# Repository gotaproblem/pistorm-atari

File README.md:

# PiStorm 4 Atari

# Join us on Discord

* There's a Discord server dedicated to PiStorm Atari discussion and development, which you can join through this handy invite link: https://discord.gg/XFEBA8QDzQ

* **IMPORTANT NOTE: Selling blank or complete PCBs or derivatives on eBay or elsewhere for excessive profit is frowned upon and may lead to forthcoming related projects being closed source.**
* Even with the current global chip shortage (October 2021), components are not **so** expensive that you should pay up to a hundred dollars or Euros for a board.
* The PiStorm is not a project for making money, it is meant to be an affordable way to replace and extend the functionality of EOL Motorola 68000 processors and have fun in the process.
* This is not meant to discourage you from making PiStorm boards for others to enjoy, but for instance selling the product as a commercial item and then pawning off support to the community if something doesn't work is absolutely not good™.

# Project information

* This fork is solely for the Atari platform. All Amiga code has been removed.
* Development is ongoing on an Atari STe, utilising an exxos PLLC adapter board to allow the fitting of the PiStorm interface. The ongoing work is a "proof-of-concept". If proven to offer acceptable performance, then bespoke hardware will be needed to allow installation within the confines of the Atari ST platforms. **If you are lucky enough to own a Phoenix H5 board (exxos shop), then the PiStorm with Pi4 fits nicely :)**
* The Atari platform differs greatly to the Amiga platform. The Atari ST uses the FC signals, interrups and bus arbitration.
* ~~Initial development was on a PI3B, but performance was poor. A PI3A+ was tried and again the performance was poor. Finally, a PI4B was tried. Although initial performance was still poor in comparison to the Amiga, there was headroom for improvemnt. Over many months, performance has slowly increased, and at time of writing, performance is finally acceptable.~~

**NOTE**

The current builds require a Pi4. This hopefully will change once a stable solution is found.
The current firmware may not work with PiSTorm boards using 74LVC16374 latches. It's a case of trying and seeing. All efforts are being made to correct this.

~~PiStorm must have 374 latches. Any other are known not to be compatible for the moment.~~
~~Sep 2023 - Firmware development has resolved the different latch/flip-flop type dependancy. Meaning, both 373 and 374 parts now work.~~
~~Sep 2023 - Pi3A+ now offers acceptible performance~~
~~Oct 2023 - Pi3B is working but needs to be overclocked~~
~~Oct 2023 - Pi Zero 2W is working but needs to be overslocked~~

Jun 2025 - Only use the latest branch. Anything before the jan2025 branch is obsolete

# Extended functionality

A virtual IDE interface is included which allows for two disk drive images to be attached, each up to 8GB in size. 
**UPDATE Oct 2023**
An additional three virtual IDE interfaces are now included, allowing for a total of eight disk drive images - a potential 64GB of disk space.

* Atari ST ROM images can be loaded at initialisation. For example, the emulation can boot using TOS 1.04 (ST only), TOS 1.06, TOS 1.62, TOS 2.06 or even EMUTos
* Alt-RAM/TT-RAM option can be added (68020, 68030, 68040 only), to increase performance
* 68020 CPU can be used with an FPU
* ET4000 SVGA graphics is now available with 1MB VRAM
* Screen grabs can be taken when using ET4000
* Additional interfaces will be added with time

# Now to get up-and-running
The following steps require basic knowledge of the linux operating system. Take your time!

* Download Raspberry Pi OS from https://www.raspberrypi.org/software/operating-systems/, you need the 32 bit Lite version.
**NOTE**
* Atari PiStorm installation has been tested with Bullseye and Bookworm

* Write the Image to an SD card. For development, a 32 GB SD card is recommended.
* Connect an HDMI Display and a USB keyboard to the Raspberry Pi.
* Insert the SD card into the Raspberry Pi4, and connect it to power. You should see a Rainbow colored screen on the HDMI Monitor followed by the booting sequence.
* When the boot process is finished (on the first run it reboots automatically after resizing the filesystems to your SD) you should be greeted with the login prompt.
* Log in as the default user, typically user: `pi` and password: `raspberry`. (The keyboard is set to US Layout on first boot!)
* Run `sudo raspi-config`
* Set up your preferences like keyboard layout, language, etc. It is recommended to set the screen resolution to 1280x720.
* Set up your Wi-Fi credentials
* Enable SSH at boot time
* Exit raspi-config

You can now reach the Pi over SSH, check your router web/settings page to find the IP of the PiStorm, or run `ifconfig` locally on the Pi from the console.

Now the final steps to get things up and running, all of this is done from a command prompt (terminal) either locally on the Pi or over ssh:
* `sudo apt-get update`
* `sudo apt full-upgrade` (If you get mysterious 'not found' messages from running the line in the next step.)
* ~~`sudo apt-get install git libasound2-dev`~~
* `sudo apt-get install git ffmpeg`
* `git clone https://github.com/gotaproblem/pistorm-atari`
* `cd pistorm-atari`
* `make clean`
**NOTE**
If using a Pi3, make must be given an option
* `make PIMODEL=PI3`
If using a Pi4, no option is needed
* `make`

~~**STRAM CACHE**~~
~~The experimental full memory cache-enabled version may be built with~~
~~* `make CACHE=ON`~~
~~or~~
~~* `make POMODEL=PI3 CACHE=ON`~~

~~This feature greatly improves STRAM read operations (and hence is mostly applicable to games), but is not yet compatible with operation of the Blitter, so please disable this at the Desktop.~~

Copy the linux boot configuration file:
* `sudo cp configs/config.txt /boot/`

Append the following to your /boot/cmdline.txt file
* `quiet vt.global_cursor_default=0 fsck.mode=force fsck.repair=yes`
**NOTE**
Do not add new-lines to this file. The entries must be one continuous line

Congratulate yourself - You've gotten this far! Shutdown the linux operating system
* `sudo halt`

# Install the hardware
**Power Caution**

How do you intend to power this thing? There are two possibilities
* 1 - power via the Atari
This is okay for the final-cut, but for development, option 2 is suggested
* 2 - power via USB
If you are developing, which requires numerous power cycles, then this is the option for you. You will need to make sure USB power (5v) does not reach the PiStorm. The Pi GPIO header supplies 5v power on pins 2 and 4. These two pins need to be cut.
As the Pi physically can not connect directly to the PiStorm, a header extension is needed - this is where you cut the pins - **do not cut the pins on the Raspberry Pi header.**
**NOTE**
DO NOT APPLY POWER FROM MULTIPLE SOURCES

If using a Pi4, a Header extension is needed, such as

https://www.amazon.co.uk/gp/product/B08C581XHV/ref=ppx_yo_dt_b_asin_title_o03_s00?ie=UTF8&th=1

https://www.amazon.co.uk/gp/product/B07NQ5Z7Y9/ref=ppx_yo_dt_b_asin_title_o04_s00?ie=UTF8&psc=1

* Attach the Pi to the PiStorm and install the PiStorm adapter in place of the orignal CPU in the Atari.
  Make sure the PiStorm sits flush and correct in the socket.
  Double check that all is properly in place and no pins are bent.

# FPGA bitstream update :
Before we can use the PiStorm, it needs to have firmware installed. 

~~Install OpenOCD:~~
~~**NOTE - v0.11 needed**~~
~~Check your openocd version~~
~~* `openocd -v`~~
~~If you have version 0.12 or later, follow these instructions:~~
~~* `sudo apt-get remove openocd`~~
~~* `sudo apt-get install openocd=0.11.0~rc2-1`~~

~~Run the FPGA update with `./flash.sh`, this will automatically detect your CPLD variant and flash appropriately.~~

~~If successful "Flashing successful!" will appear, if not it will fail with "Flashing failed" and `nprog_log.txt` will be created with more details.~~

Dec 2023 - openocd is no longer used

* Flash the PiStorm firmware using the included tool - replace xxx with your CPLD type eg. EPM240 or EPM570
`rtl/pistormflash -s rtl/EPMxxx_bitstream.svf`
Expect a "Warning" to be shown. This can be ignored.

# Running

**Testing**

As a confidence test, it is suggested you run ataritest to confirm basic functionality.
* `sudo ./ataritest --memory tests=rw`
If you see any errors, then discuss in the discord development channel. 

ataritest can do a lot more, like reading and writing (peek and poke), to Atari memory space, filling Atari memory with patterns.

**Setup file structure**

From the pistorm-atari directory, perform the following commands
* `mkdir ../roms`
* `mkdir ../dkimages`
* `mkdir ../configs`
* `mkdir ../screendumps`
* `cp configs/atari.cfg ../configs`
* `cp roms/roms.zip ../roms/`
* `cd ../roms`
* `unzip roms.zip`
* `cd ../pistorm-atari`

**Starting the Emulator**

Start the emulator with the default Atari configuration by typing `sudo ./emulator --config ../configs/atari.cfg`

A couple of disk images have been created to help you get started. These are optional. You could of course run programmes off your 
floppy disk drive and/or an attached ACSI bus device.

**The disk images are too large for GitHub. Please find the disk images at https://bbansolutions.co.uk**
Download the disks.zip file, copy to ../dkimages/ directory. Uncompress the file to give two disk images.
* `cd ../dkimages`
* `wget http://bbansolutions.co.uk/wp-content/uploads/2023/10/disks.zip`
* `unzip disks.zip`
* `cd ../pistorm-atari`

Run the emulator using `sudo ./emulator --config ../configs/atari.cfg`.

To exit the emulator you can press `Ctrl+C`.

# RTG Graphics ~~- Raylib~~
Sep 2023 - no-longer using raylib

Enhanced video modes are available for GEM and Mint.
* Changes to the emulator configuration file are needed
* edit your .cfg file and uncomment (remove the preceding hash), the following line
* #setvar rtg

**A mint specific configuration file is now included in the repository**
* Make a copy of configs/mint.cfg
* `cp configs/mint.cfg ../configs/`

~~Finally, perform a rebuild~~
~~To build now, using RTG, you must alter the git branch before compiling~~
~~* `git checkout et4000-dev`~~
~~* `make clean`~~
~~* `make`~~

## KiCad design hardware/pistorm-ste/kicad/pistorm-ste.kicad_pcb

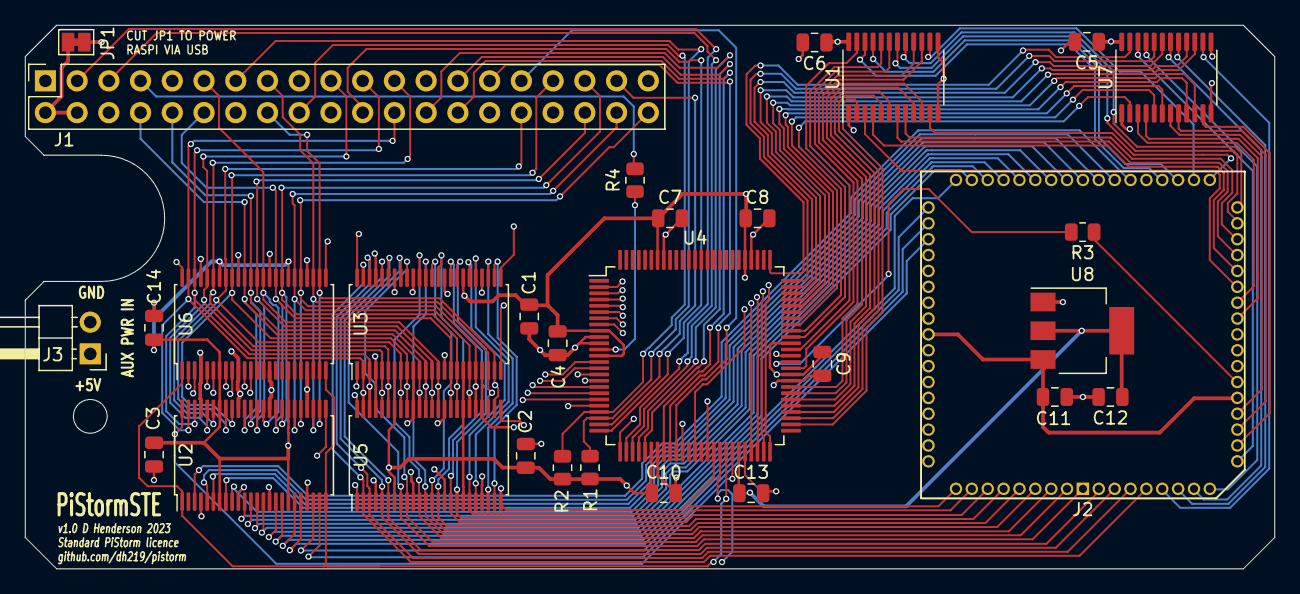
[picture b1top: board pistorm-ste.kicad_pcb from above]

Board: 4 copper layers, 100.0 x 43.5 mm, 30 parts (0 on the bottom side), 125 nets.

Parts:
C1, C2, C3, C4, C5, C6, C7, C8, C9, C10, C13, C14: 100n; C_0805_2012Metric
C11, C12: 22u; C_0805_2012Metric
J1: Raspberry_Pi_2_3; PinSocket_2x20_P2.54mm_Vertical
J2: PLCC68_plug; PLCC68_male_pins
J3: Conn_01x02_Male; PinHeader_1x02_P2.54mm_Horizontal
JP1: SolderJumper_2_Bridged; SolderJumper-2_P1.3mm_Bridged_Pad1.0x1.5mm
R1, R2: 4k7; R_0805_2012Metric
R3, R4: 0-100R; R_0805_2012Metric
U1, U7: SN54CBTD3384; TSSOP-24_4.4x7.8mm_P0.65mm
U2, U3, U5, U6: SN74LVC16373; TSSOP-48_6.1x12.5mm_P0.5mm
U4: EPM240T100; LQFP-100_14x14mm_P0.5mm
U8: LM1117-3.3; SOT-223-3_TabPin2

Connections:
+3V3: C1.1, C2.1, C3.1, C4.1, C7.1, C8.1, C9.1, C10.1, C12.1, C13.1, C14.1, R1.1, R2.1, U2.7 (VCC), U2.18 (VCC), U2.31 (VCC), U2.42 (VCC), U3.7 (VCC), U3.18 (VCC), U3.31 (VCC), U3.42 (VCC), U4.9 (VCCIO1), U4.13 (VCCINT), U4.31 (VCCIO1), U4.45 (VCCIO1), U4.59 (VCCIO2), U4.63 (VCCINT), U4.80 (VCCIO2), U4.94 (VCCIO2), U5.7 (VCC), U5.18 (VCC), U5.31 (VCC), U5.42 (VCC), U6.7 (VCC), U6.18 (VCC), U6.31 (VCC), U6.42 (VCC), U8.2 (VO)
+5V: C5.1, C6.1, C11.1, J2.14, J2.52, J3.1, JP1.1 (A), U1.24 (VCC), U7.24 (VCC), U8.3 (VI)
/+5V_PI: J1.2 (5V), J1.4 (5V), JP1.2 (B)
/A1: J2.32, U2.3 (1Q2)
/A2: J2.33, U2.5 (1Q3)
/A3: J2.34, U2.6 (1Q4)
/A4: J2.35, U2.8 (1Q5)
/A5: J2.36, U2.9 (1Q6)
/A6: J2.37, U2.11 (1Q7)
/A7: J2.38, U2.12 (1Q8)
/A8: J2.39, U2.13 (2Q1)
/A9: J2.40, U2.14 (2Q2)
/A10: J2.41, U2.16 (2Q3)
/A11: J2.42, U2.17 (2Q4)
/A12: J2.43, U2.19 (2Q5)
/A13: J2.44, U2.20 (2Q6)
/A14: J2.45, U2.22 (2Q7)
/A15: J2.46, U2.23 (2Q8)
/A16: J2.47, U6.2 (1Q1)
/A17: J2.48, U6.3 (1Q2)
/A18: J2.49, U6.5 (1Q3)
/A19: J2.50, U6.6 (1Q4)
/A20: J2.51, U6.8 (1Q5)
/A21: J2.53, U6.9 (1Q6)
/A22: J2.54, U6.11 (1Q7)
/A23: J2.55, U6.12 (1Q8)
/ADDR_LTCH_0: U2.48 (1LE), U4.44 (IO1_44/DEV_CLRn)
/ADDR_LTCH_8: U2.25 (2LE), U4.42 (IO1_42)
/ADDR_LTCH_16: U4.47 (IO1_47), U6.48 (1LE)
/ADDR_LTCH_24: U4.48 (IO1_48), U6.25 (2LE)
/ADDR_OE: U2.1 (1OE), U2.24 (2OE), U4.43 (IO1_43/DEV_OE), U6.1 (1OE), U6.24 (2OE)
/AS: J2.6, U7.14 (2A1)
/AS_3: U4.72 (IO2_72), U7.15 (2B1)
/AUX0: J1.27 (ID_SD/GPIO0), U4.30 (IO1_30)
/AUX1: J1.28 (ID_SC/GPIO1), U4.33 (IO1_33)
/BERR: J2.24, U1.8 (1A4)
/BERR_3: U1.9 (1B4), U4.55 (IO2_55)
/BG: J2.11, U7.11 (1A5)
/BGACK: J2.12, U7.8 (1A4)
/BGACK_3: U4.70 (IO2_70), U7.9 (1B4)
/BG_3: U4.71 (IO2_71), U7.10 (1B5)
/BR: J2.13, U7.7 (1A3)
/BR_3: U4.69 (IO2_69), U7.6 (1B3)
/CLK: R3.2, U4.62 (IO2_62/GCLK2)
/CLK_STE: J2.15, R3.1
/D0: J2.5, U3.47 (1D1), U5.2 (1Q1)
/D1: J2.4, U3.46 (1D2), U5.3 (1Q2)
/D2: J2.3, U3.44 (1D3), U5.5 (1Q3)
/D3: J2.2, U3.43 (1D4), U5.6 (1Q4)
/D4: J2.1, U3.41 (1D5), U5.8 (1Q5)
/D5: J2.68, U3.40 (1D6), U5.9 (1Q6)
/D6: J2.67, U3.38 (1D7), U5.11 (1Q7)
/D7: J2.66, U3.37 (1D8), U5.12 (1Q8)
/D8: J2.65, U3.36 (2D1), U5.13 (2Q1)
/D9: J2.64, U3.35 (2D2), U5.14 (2Q2)
/D10: J2.63, U3.33 (2D3), U5.16 (2Q3)
/D11: J2.62, U3.32 (2D4), U5.17 (2Q4)
/D12: J2.61, U3.30 (2D5), U5.19 (2Q5)
/D13: J2.60, U3.29 (2D6), U5.20 (2Q6)
/D14: J2.59, U3.27 (2D7), U5.22 (2Q7)
/D15: J2.58, U3.26 (2D8), U5.23 (2Q8)
/DATA_RD_LTCH_HB: U3.25 (2LE), U4.50 (IO1_50)
/DATA_RD_LTCH_LB: U3.48 (1LE), U4.49 (IO1_49)
/DATA_RD_OE: U3.1 (1OE), U3.24 (2OE), U4.38 (IO1_38)
/DATA_WR_LTCH_HB: U4.36 (IO1_36), U5.25 (2LE)
/DATA_WR_LTCH_LB: U4.40 (IO1_40), U5.48 (1LE)
/DATA_WR_OE: U4.41 (IO1_41), U5.1 (1OE), U5.24 (2OE)
/DTACK: J2.10, U7.22 (2A5)
/DTACK_3: U4.76 (IO2_76), U7.23 (2B5)
/E: J2.22, U1.4 (1A2)
/E_3: U1.5 (1B2), U4.53 (IO2_53)
/FC0: J2.30, U1.22 (2A5)
/FC0_3: U1.23 (2B5), U4.66 (IO2_66)
/FC1: J2.29, U1.21 (2A4)
/FC1_3: U1.20 (2B4), U4.64 (IO2_64/GCLK3)
/FC2: J2.28, U1.14 (2A1)
/FC2_3: U1.15 (2B1), U4.57 (IO2_57)
/HALT: J2.19, U7.4 (1A2)
/HALT_3: U4.68 (IO2_68), U7.5 (1B2)
/IPL0: J2.27, U1.11 (1A5)
/IPL0_3: U1.10 (1B5), U4.56 (IO2_56)
/IPL1: J2.26, U1.17 (2A2)
/IPL1_3: U1.16 (2B2), U4.58 (IO2_58)
/IPL2: J2.25, U1.18 (2A3)
/IPL2_3: U1.19 (2B3), U4.61 (IO2_61)
/LDS: J2.8, U7.18 (2A3)
/LDS_3: U4.74 (IO2_74), U7.19 (2B3)
/PICLK: R4.2, U4.12 (IO1_12/GCLK0)
/PICLK_OUT: J1.7 (GCLK0/GPIO4), R4.1
/RESET: J2.20, U7.3 (1A1)
/RESET_3: U4.67 (IO2_67), U7.2 (1B1)
/RW: J2.9, U7.21 (2A4)
/RW_3: U4.75 (IO2_75), U7.20 (2B4)
/SA0: J1.29 (GCLK1/GPIO5), U4.34 (IO1_34)
/SA1: J1.5 (SCL/GPIO3), U4.28 (IO1_28)
/SA2: J1.3 (SDA/GPIO2), U4.27 (IO1_27)
/SD0: J1.24 (~CE0/GPIO8), U2.47 (1D1), U3.2 (1Q1), U4.2 (IO1_2), U5.47 (1D1), U6.47 (1D1)
/SD1: J1.21 (MISO0/GPIO9), U2.46 (1D2), U3.3 (1Q2), U4.3 (IO1_3), U5.46 (1D2), U6.46 (1D2)
/SD2: J1.19 (MOSI0/GPIO10), U2.44 (1D3), U3.5 (1Q3), U4.4 (IO1_4), U5.44 (1D3), U6.44 (1D3)
/SD3: J1.23 (SCLK0/GPIO11), U2.43 (1D4), U3.6 (1Q4), U4.5 (IO1_5), U5.43 (1D4), U6.43 (1D4)
/SD4: J1.32 (PWM0/GPIO12), U2.41 (1D5), U3.8 (1Q5), U4.6 (IO1_6), U5.41 (1D5), U6.41 (1D5)
/SD5: J1.33 (PWM1/GPIO13), U2.40 (1D6), U3.9 (1Q6), U4.7 (IO1_7), U5.40 (1D6), U6.40 (1D6)
/SD6: J1.8 (GPIO14/TXD), U2.38 (1D7), U3.11 (1Q7), U4.26 (IO1_26), U5.38 (1D7), U6.38 (1D7)
/SD7: J1.10 (GPIO15/RXD), U2.37 (1D8), U3.12 (1Q8), U4.21 (IO1_21), U5.37 (1D8), U6.37 (1D8)
/SD8: J1.36 (GPIO16), U2.36 (2D1), U3.13 (2Q1), U4.17 (IO1_17), U5.36 (2D1), U6.36 (2D1)
/SD9: J1.11 (GPIO17), U2.35 (2D2), U3.14 (2Q2), U4.16 (IO1_16), U5.35 (2D2), U6.35 (2D2)
/SD10: J1.12 (GPIO18/PWM0), U2.33 (2D3), U3.16 (2Q3), U4.20 (IO1_20), U5.33 (2D3), U6.33 (2D3)
/SD11: J1.35 (GPIO19/MISO1), U2.32 (2D4), U3.17 (2Q4), U4.8 (IO1_8), U5.32 (2D4), U6.32 (2D4)
/SD12: J1.38 (GPIO20/MOSI1), U2.30 (2D5), U3.19 (2Q5), U4.15 (IO1_15), U5.30 (2D5), U6.30 (2D5)
/SD13: J1.40 (GPIO21/SCLK1), U2.29 (2D6), U3.20 (2Q6), U4.14 (IO1_14/GCLK1), U5.29 (2D6), U6.29 (2D6)
/SD14: J1.15 (GPIO22), U2.27 (2D7), U3.22 (2Q7), U4.19 (IO1_19), U5.27 (2D7), U6.27 (2D7)
/SD15: J1.16 (GPIO23), U2.26 (2D8), U3.23 (2Q8), U4.18 (IO1_18), U5.26 (2D8), U6.26 (2D8)
/SOE: J1.31 (GCLK2/GPIO6), U4.35 (IO1_35)
/SWE: J1.26 (~CE1/GPIO7), U4.29 (IO1_29)
/TCK: J1.37 (GPIO26), U4.24 (TCK)
/TDI: J1.13 (GPIO27), R1.2, U4.23 (TDI)
/TDO: J1.22 (GPIO25), U4.25 (TDO)
/TMS: J1.18 (GPIO24), R2.2, U4.22 (TMS)
/UDS: J2.7, U7.17 (2A2)
/UDS_3: U4.73 (IO2_73), U7.16 (2B2)
/VMA: J2.21, U1.3 (1A1)
/VMA_3: U1.2 (1B1), U4.52 (IO2_52)
/VPA: J2.23, U1.7 (1A3)
/VPA_3: U1.6 (1B3), U4.54 (IO2_54)
GND: C1.2, C2.2, C3.2, C4.2, C5.2, C6.2, C7.2, C8.2, C9.2, C10.2, C11.2, C12.2, C13.2, C14.2, J1.6 (GND), J1.9 (GND), J1.14 (GND), J1.20 (GND), J1.25 (GND), J1.30 (GND), J1.34 (GND), J1.39 (GND), J2.16, J2.17, J2.56, J2.57, J3.2, U1.1 (1OE), U1.12 (GND), U1.13 (2OE), U2.4 (GND), U2.10 (GND), U2.15 (GND), U2.21 (GND), U2.28 (GND), U2.34 (GND), U2.39 (GND), U2.45 (GND), U3.4 (GND), U3.10 (GND), U3.15 (GND), U3.21 (GND), U3.28 (GND), U3.34 (GND), U3.39 (GND), U3.45 (GND), U4.10 (GNDIO), U4.11 (GNDINT), U4.32 (GNDIO), U4.46 (GNDIO), U4.60 (GNDIO), U4.65 (GNDINT), U4.79 (GNDIO), U4.93 (GNDIO), U5.4 (GND), U5.10 (GND), U5.15 (GND), U5.21 (GND), U5.28 (GND), U5.34 (GND), U5.39 (GND), U5.45 (GND), U6.4 (GND), U6.10 (GND), U6.15 (GND), U6.21 (GND), U6.28 (GND), U6.34 (GND), U6.39 (GND), U6.45 (GND), U7.1 (1OE), U7.12 (GND), U7.13 (2OE), U8.1 (GND)

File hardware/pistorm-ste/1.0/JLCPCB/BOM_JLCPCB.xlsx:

Comment | Designator | Footprint | JLCPCB Part #（optional）
100nF | C1,C2,C3,C4,C5,C6,C7,C8,C9,C10,C13,C14 | 0805 | C49678
22uF | C11, C12 | 0805 | C45783
4.7K | R1, R2 | 0805 | C60816
10R | R3,R4 | 0805 | C96347
SN74CBTD3384PW | U1, U7 | TSSOP-24 | C7155
SN74LVC16373DGGR | U2, U3, U5, U6 | TSSOP-48 | C282344
EPM240T100C5N | U4 | TQFP100_N | C10041
LM1117IMPX-3.3 | U8 | SOT-223-3 | C23984

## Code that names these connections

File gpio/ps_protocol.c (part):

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//#define IO_DEBUG 

//#define CHECK_IRQ(x) (!(x & 0x02) ) // if there is an interrupt, return positive
#define CHECK_IRQ(x) (((x & 0x10) >> 2) | (x & 0x02)) // only using IPL1 and IPL2, these are on GPIO 1 & 4
#define CHECK_BERR(x) (!(x & 0x20) ) // if there is a BERR, return positive

/* clear output bits only */
//#define TXN_END 0xffffff //0xffffde // don't clear bits 5, 0 // 0xffffcc //0xffffec
//#define TXN_END 0xffff8c
#define TXN_END 0xffffcc
//#define PIN_BERR PIN_RESET

#ifdef STATS
t_stats RWstats;
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#endif


/* Enable PI_CLK output on GPIO4, adjust divider and pll source depending on pi model */
static void setup_gpclk ( int targetF ) 
{
  int cpuf, coref;
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
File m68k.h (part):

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void m68k_modify_timeslice(int cycles); /* Modify cycles left */
void m68k_end_timeslice(void);          /* End timeslice now */

/* Set the IPL0-IPL2 pins on the CPU (IRQ).
 * A transition from < 7 to 7 will cause a non-maskable interrupt (NMI).
 * Setting IRQ to 0 will clear an interrupt request.
 */
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void m68k_set_virq(unsigned int level, unsigned int active);
unsigned int m68k_get_virq(unsigned int level);

/* Halt the CPU as if you pulsed the HALT pin. */
void m68k_pulse_halt(void);


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
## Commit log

2023-02-03 IDE fix for 32bit CPUs
2023-02-03 IDE fix for 32bit CPU's
2023-02-18 Performance optimisations
2023-04-08 pi4 + tailored for atari only
2023-06-23 PI4 optimisations
2023-06-23 Atari specific
2023-06-23 config stuff
2023-06-23 config files
2023-06-23 ammended README
2023-06-23 README updated
2023-06-23 add missing files
2023-06-24 remove obsolete files
2023-06-24 better instruction
2023-06-24 testing performance
2023-06-24 stability
2023-06-25 IDE fix
2023-07-03 added HDMI output for native resolutions
2023-07-03 correct hdmi settings
2023-07-04 enhanced brightness
2023-07-05 Raylib feature added for RTG
2023-07-05 mapping index correction
2023-07-13 tidy up
2023-08-24 et4000 integration
2023-08-24 add missing et4000 files
2023-09-09 RTG graphics support
2023-09-09 update instructions
2023-09-16 ST RTG fixes
2023-09-16 added screengrab function
2023-09-30 Pi3/Pi4 unification + screendump addition + IDE fix
2023-09-30 Pi3 alterations
2023-09-30 documentation updates
2023-09-30 resolved Pi4 clock setup - primarily for H5
2023-09-30 corrected filter order
2023-10-01 autoboot script mods
2023-10-01 autoboot mods
2023-10-03 fixed soft reset issue
2023-10-03 rtg init fixed
2023-10-03 deleted raylib stuff and added RTC interface
2023-10-05 added Atari logo
2023-10-06 add verilog
2023-10-10 removed [pi3] problem entries
2023-10-14 added tools and updated firmware
2023-10-14 IDE x4 development
2023-10-16 added pi zero 2w filter
2023-10-24 fixed possible IDE channel mis-addressing
2023-10-25 use bmp for Logo, resolve IDE issues
2023-10-25 resolved frame updates
2023-10-26 Adding experimental full-RAM cache
2023-10-26 Adding the hardware design files for PiStormSTE
2023-10-27 Adding production files for PiStormSTE; moving the kicad directory into hardware.
2023-10-29 ET4000 improvements
2023-10-29 added additional resolutions
2023-10-30 undo ps_protocol.c mistakes
2023-10-30 corrected syntax error
2023-10-30 correct
2023-11-01 new RTC switch added
2023-11-01 dynamic clock configuration
2023-11-01 changed some symbol names
2023-11-01 optimised WTC
2023-11-01 removed blitter disable
2023-11-21 blitter experiment + performance + stability
2023-11-21 firmware stability
2023-11-28 testing for pi3 stability
2023-11-30 stability fixes
2023-11-30 use dh219 wtc
2023-12-01 physical memory check correction
2023-12-01 physical RAM check fixed
2023-12-02 stability for new firmware
2023-12-03 remove test deley loops
2023-12-03 latest firmware
2023-12-06 revised firmware flashing method
2023-12-25 latest and greatest
2024-01-07 stability changes
2024-01-11 et4000 stability
2024-05-12 may development
2024-05-12 latest pi4 bitstream source
2025-01-17 January 2025 updates
2025-01-19 firmware update
2025-01-19 corrected pi4 settings
2025-01-26 corrected working directory
2025-01-26 RTG stability and HDD correction for /dev/loop

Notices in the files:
gpio/ps_protocol.c:
SPDX-License-Identifier: MIT
Original Copyright 2020 Claude Schwarz
m68k.h:
Copyright Karl Stenerud.  All rights reserved.
